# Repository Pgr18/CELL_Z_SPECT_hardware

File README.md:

# CELL_Z_SPECT_hardware
Печатные платы для проекта клеточной импедансной спектроскопии

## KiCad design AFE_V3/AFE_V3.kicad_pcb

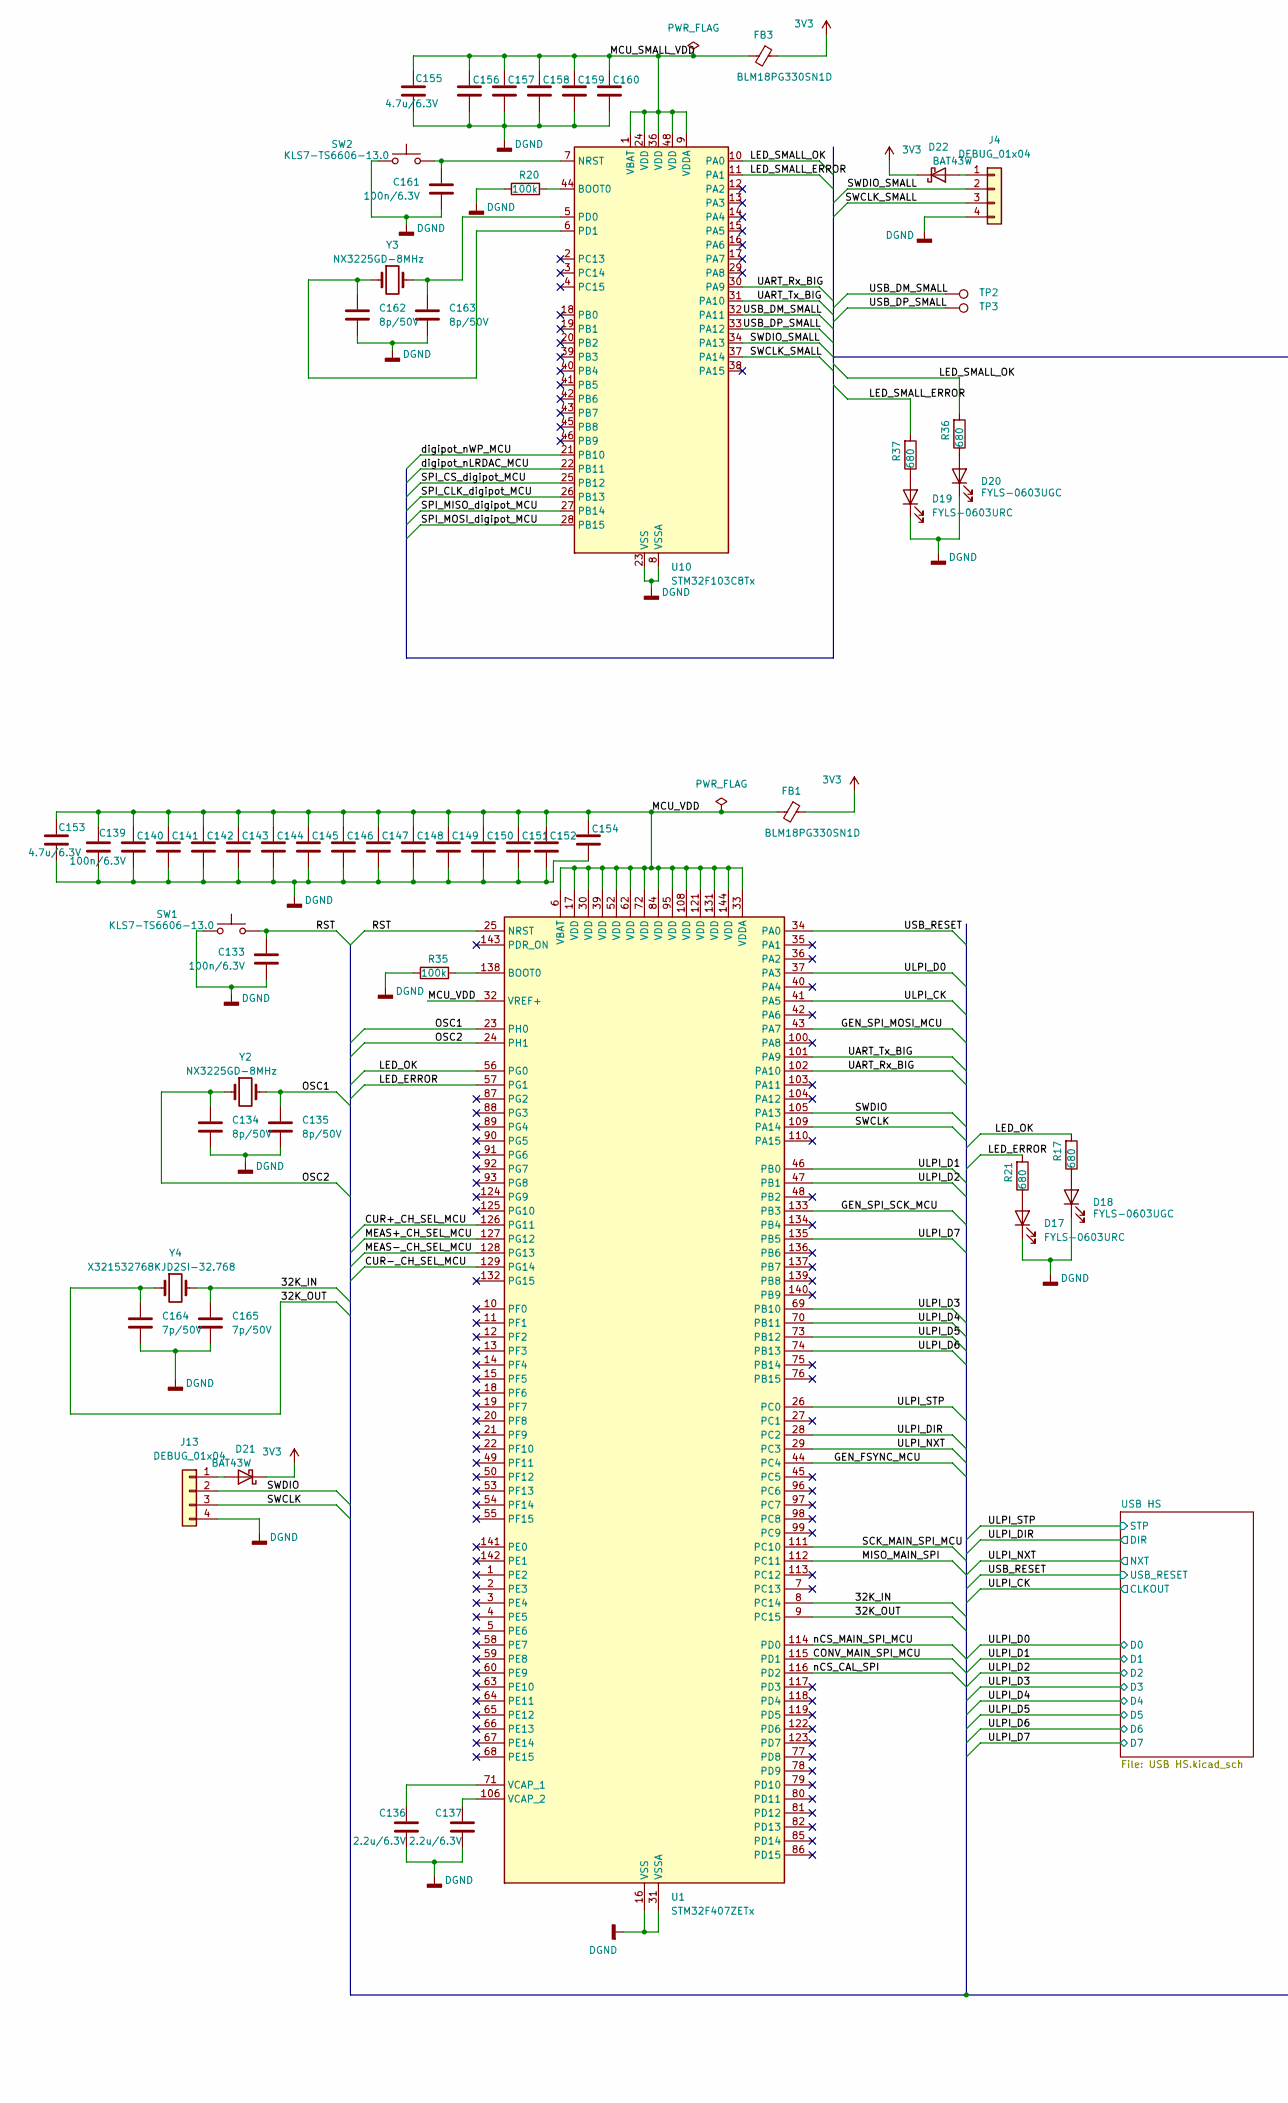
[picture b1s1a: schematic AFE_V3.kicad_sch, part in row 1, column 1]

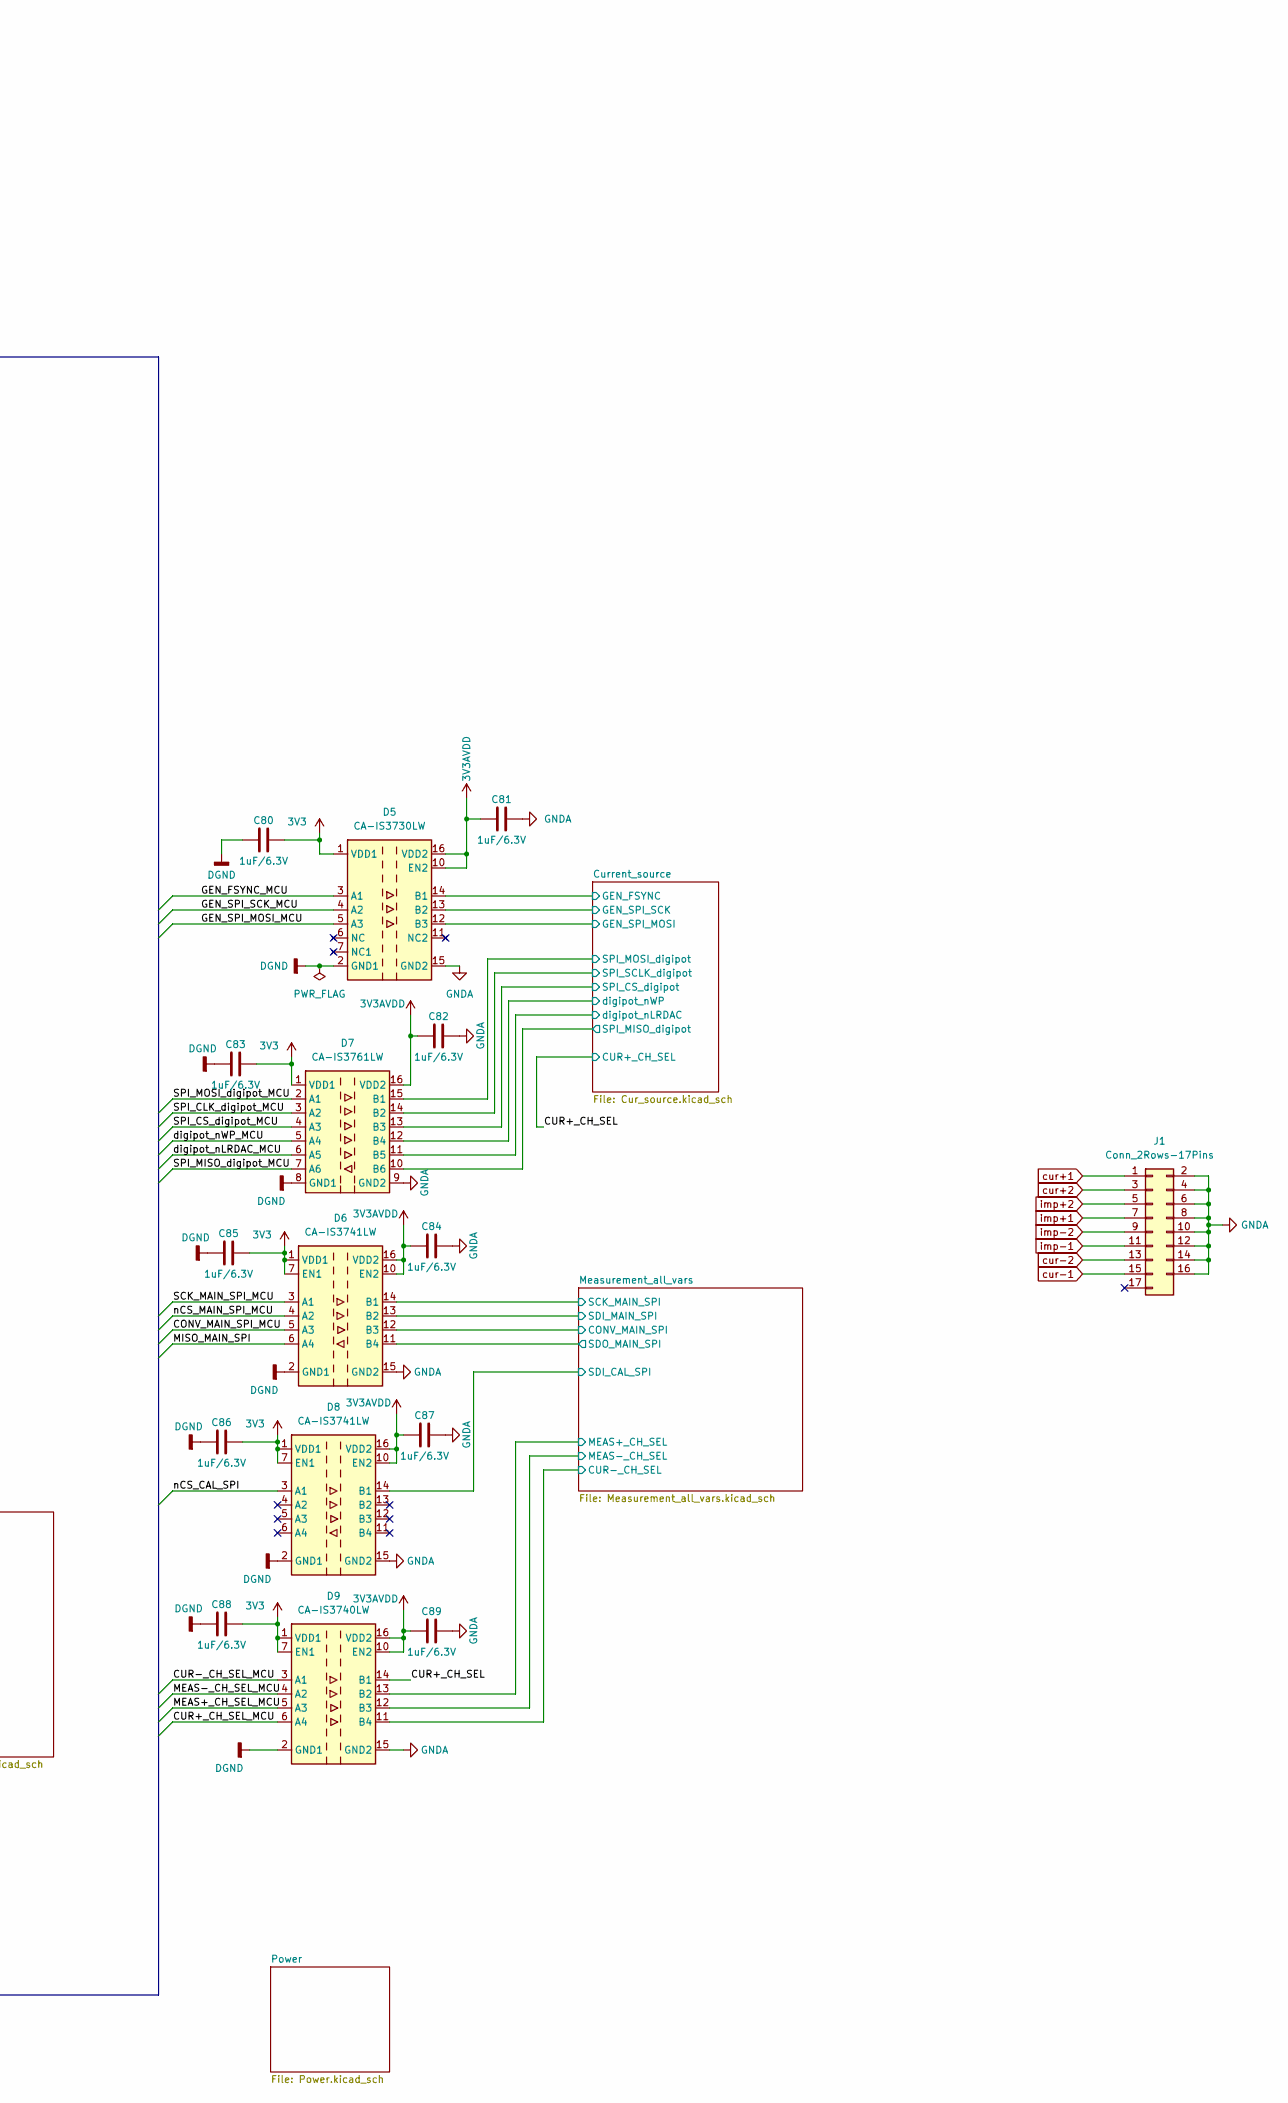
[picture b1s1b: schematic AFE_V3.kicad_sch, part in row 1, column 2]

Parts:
C80, C81, C82, C83, C84, C85, C86, C87, C88, C89: 1uF/6.3V; C_0603_1608Metric_Pad1.08x0.95mm_HandSolder
C133, C139, C140, C141, C142, C143, C144, C145, C146, C147, C148, C149, C150, C151, C152, C154, C156, C157, C158, C159, C160, C161: 100n/6.3V; C_0402_1005Metric
C134, C135, C162, C163: 8p/50V; C_0603_1608Metric_Pad1.08x0.95mm_HandSolder
C136, C137: 2.2u/6.3V; C_0805_2012Metric_Pad1.18x1.45mm_HandSolder
C153, C155: 4.7u/6.3V; C_0805_2012Metric_Pad1.18x1.45mm_HandSolder
C164, C165: 7p/50V; C_0603_1608Metric_Pad1.08x0.95mm_HandSolder
D5: CA-IS3730LW; SOIC-16W_7.5x10.3mm_P1.27mm
D6, D8: CA-IS3741LW; SOIC-16W_7.5x10.3mm_P1.27mm
D7: CA-IS3761LW; SOIC-16W_7.5x10.3mm_P1.27mm
D9: CA-IS3740LW; SOIC-16W_7.5x10.3mm_P1.27mm
D17, D19: FYLS-0603URC; LED_0603_1608Metric_Pad1.05x0.95mm_HandSolder
D18, D20: FYLS-0603UGC; LED_0603_1608Metric_Pad1.05x0.95mm_HandSolder
D21, D22: BAT43W; D_SOD-123
FB1, FB3: BLM18PG330SN1D; L_0603_1608Metric_Pad1.05x0.95mm_HandSolder
J1: Conn_2Rows-17Pins; PinHeader_2x08_P2.54mm_Horizontal
J4, J13: DEBUG_01x04; PinHeader_1x04_P2.54mm_Vertical
R17, R21, R36, R37: 680; R_0603_1608Metric_Pad0.98x0.95mm_HandSolder
R20, R35: 100k; R_0603_1608Metric_Pad0.98x0.95mm_HandSolder
SW1, SW2: KLS7-TS6606-13.0; SW_PUSH_6mm_H4.3mm
TP2, TP3: TestPoint_Pad_D1.0mm
U1: STM32F407ZETx; LQFP-144_20x20mm_P0.5mm
U10: STM32F103C8Tx; LQFP-48_7x7mm_P0.5mm
Y2, Y3: NX3225GD-8MHz; NX3225GD
Y4: X321532768KJD2SI-32.768; Crystal_SMD_3215-2Pin_3.2x1.5mm

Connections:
3V3: C80.2, C83.2, C85.2, C86.2, C88.2, D5.1 (VDD1), D6.1 (VDD1), D6.7 (EN1), D7.1 (VDD1), D8.1 (VDD1), D8.7 (EN1), D9.1 (VDD1), D9.7 (EN1), D21.1 (K), D22.1 (K), FB1.1, FB3.1; also elsewhere on the board
3V3AVDD: C81.1, C82.1, C84.1, C87.1, C89.1, D5.10 (EN2), D5.16 (VDD2), D6.10 (EN2), D6.16 (VDD2), D7.16 (VDD2), D8.10 (EN2), D8.16 (VDD2), D9.10 (EN2), D9.16 (VDD2); also elsewhere on the board
/32K_IN: C165.2, U1.8 (PC14), Y4.2
/32K_OUT: C164.2, U1.9 (PC15), Y4.1
/CONV_MAIN_SPI_MCU: D6.5 (A3), U1.115 (PD1)
/CUR+_CH_SEL: D9.14 (B1); also elsewhere on the board
/CUR+_CH_SEL_MCU: D9.6 (A4), U1.126 (PG11)
/CUR-_CH_SEL_MCU: D9.3 (A1), U1.129 (PG14)
/Current_source/GEN_FSYNC: D5.14 (B1); also elsewhere on the board
/Current_source/GEN_SPI_MOSI: D5.12 (B3); also elsewhere on the board
/Current_source/GEN_SPI_SCK: D5.13 (B2); also elsewhere on the board
/Current_source/SPI_CS_digipot: D7.13 (B3); also elsewhere on the board
/Current_source/SPI_MISO_digipot: D7.10 (B6); also elsewhere on the board
/Current_source/SPI_MOSI_digipot: D7.15 (B1); also elsewhere on the board
/Current_source/SPI_SCLK_digipot: D7.14 (B2); also elsewhere on the board
/Current_source/digipot_nLRDAC: D7.11 (B5); also elsewhere on the board
/Current_source/digipot_nWP: D7.12 (B4); also elsewhere on the board
/GEN_FSYNC_MCU: D5.3 (A1), U1.44 (PC4)
/GEN_SPI_MOSI_MCU: D5.5 (A3), U1.43 (PA7)
/GEN_SPI_SCK_MCU: D5.4 (A2), U1.133 (PB3)
/LED_ERROR: R21.2, U1.57 (PG1)
/LED_OK: R17.2, U1.56 (PG0)
/LED_SMALL_ERROR: R37.2, U10.11 (PA1)
/LED_SMALL_OK: R36.2, U10.10 (PA0)
/MCU_SMALL_VDD: C155.1, C156.2, C157.2, C158.2, C159.2, C160.2, FB3.2, U10.1 (VBAT), U10.9 (VDDA), U10.24 (VDD), U10.36 (VDD), U10.48 (VDD)
/MCU_VDD: C139.2, C140.2, C141.2, C142.2, C143.2, C144.2, C145.2, C146.2, C147.2, C148.2, C149.2, C150.2, C151.2, C152.2, C153.1, C154.2, FB1.2, U1.6 (VBAT), U1.17 (VDD), U1.30 (VDD), U1.32 (VREF+), U1.33 (VDDA), U1.39 (VDD), U1.52 (VDD), U1.62 (VDD), U1.72 (VDD), U1.84 (VDD), U1.95 (VDD), U1.108 (VDD), U1.121 (VDD), U1.131 (VDD), U1.144 (VDD)
/MEAS+_CH_SEL_MCU: D9.5 (A3), U1.127 (PG12)
/MEAS-_CH_SEL_MCU: D9.4 (A2), U1.128 (PG13)
/MISO_MAIN_SPI: D6.6 (A4), U1.112 (PC11)
/Measurement_all_vars/CONV_SPI: D6.12 (B3); also elsewhere on the board
/Measurement_all_vars/CUR-_CH_SEL: D9.11 (B4); also elsewhere on the board
/Measurement_all_vars/MEAS+_CH_SEL: D9.13 (B2); also elsewhere on the board
/Measurement_all_vars/MEAS-_CH_SEL: D9.12 (B3); also elsewhere on the board
/Measurement_all_vars/SDI_CAL_SPI: D8.14 (B1); also elsewhere on the board
/Measurement_all_vars/SDI_MAIN_SPI: D6.13 (B2); also elsewhere on the board
/Measurement_all_vars/SDO_SPI: D6.11 (B4); also elsewhere on the board
/Measurement_all_vars/SPI_CLK: D6.14 (B1); also elsewhere on the board
/OSC1: C135.2, U1.23 (PH0), Y2.2
/OSC2: C134.2, U1.24 (PH1), Y2.1
/RST: C133.2, SW1.2, U1.25 (NRST)
/SCK_MAIN_SPI_MCU: D6.3 (A1), U1.111 (PC10)
/SPI_CLK_digipot_MCU: D7.3 (A2), U10.26 (PB13)
/SPI_CS_digipot_MCU: D7.4 (A3), U10.25 (PB12)
/SPI_MISO_digipot_MCU: D7.7 (A6), U10.27 (PB14)
/SPI_MOSI_digipot_MCU: D7.2 (A1), U10.28 (PB15)
/SWCLK: J13.3, U1.109 (PA14)
/SWCLK_SMALL: J4.3, U10.37 (PA14)
/SWDIO: J13.2, U1.105 (PA13)
/SWDIO_SMALL: J4.2, U10.34 (PA13)
/UART_Rx_BIG: U1.102 (PA10), U10.30 (PA9)
/UART_Tx_BIG: U1.101 (PA9), U10.31 (PA10)
/ULPI_CK: U1.41 (PA5); also elsewhere on the board
/ULPI_D0: U1.37 (PA3); also elsewhere on the board
/ULPI_D1: U1.46 (PB0); also elsewhere on the board
/ULPI_D2: U1.47 (PB1); also elsewhere on the board
/ULPI_D3: U1.69 (PB10); also elsewhere on the board
/ULPI_D4: U1.70 (PB11); also elsewhere on the board
/ULPI_D5: U1.73 (PB12); also elsewhere on the board
/ULPI_D6: U1.74 (PB13); also elsewhere on the board
/ULPI_D7: U1.135 (PB5); also elsewhere on the board
/ULPI_DIR: U1.28 (PC2); also elsewhere on the board
/ULPI_NXT: U1.29 (PC3); also elsewhere on the board
/ULPI_STP: U1.26 (PC0); also elsewhere on the board
/USB_DM_SMALL: TP2.1, U10.32 (PA11)
/USB_DP_SMALL: TP3.1, U10.33 (PA12)
/USB_RESET: U1.34 (PA0); also elsewhere on the board
/digipot_nLRDAC_MCU: D7.6 (A5), U10.22 (PB11)
/digipot_nWP_MCU: D7.5 (A4), U10.21 (PB10)
/nCS_CAL_SPI: D8.3 (A1), U1.116 (PD2)
/nCS_MAIN_SPI_MCU: D6.4 (A2), U1.114 (PD0)
DGND: C80.1, C83.1, C85.1, C86.1, C88.1, C133.1, C134.1, C135.1, C136.2, C137.2, C139.1, C140.1, C141.1, C142.1, C143.1, C144.1, C145.1, C146.1, C147.1, C148.1, C149.1, C150.1, C151.1, C152.1, C153.2, C154.1, C155.2, C156.1, C157.1, C158.1, C159.1, C160.1, C161.1, C162.1, C163.1, C164.1, C165.1, D5.2 (GND1), D5.8 (GND1), D6.2 (GND1), D6.8 (GND1), D7.8 (GND1), D8.2 (GND1), D8.8 (GND1), D9.2 (GND1), D9.8 (GND1), D17.1 (K), D18.1 (K), D19.1 (K), D20.1 (K), J4.4, J13.4, R20.1, R35.1, SW1.1, SW2.1, U1.16 (VSS), U1.31 (VSSA), U1.38 (VSS), U1.51 (VSS), U1.61 (VSS), U1.83 (VSS), U1.94 (VSS), U1.107 (VSS), U1.120 (VSS), U1.130 (VSS), U10.8 (VSSA), U10.23 (VSS), U10.35 (VSS), U10.47 (VSS); also elsewhere on the board
GNDA: C81.2, C82.2, C84.2, C87.2, C89.2, D5.9 (GND2), D5.15 (GND2), D6.9 (GND2), D6.15 (GND2), D7.9 (GND2), D8.9 (GND2), D8.15 (GND2), D9.9 (GND2), D9.15 (GND2), J1.2, J1.4, J1.6, J1.8, J1.10, J1.12, J1.14, J1.16; also elsewhere on the board
unnamed: D17.2 (A), R21.1
unnamed: D18.2 (A), R17.1
unnamed: D19.2 (A), R37.1
unnamed: D20.2 (A), R36.1
unnamed: D21.2 (A), J13.1
unnamed: D22.2 (A), J4.1
unnamed: R35.2, U1.138 (BOOT0)
unnamed: C136.1, U1.71 (VCAP_1)
unnamed: C137.1, U1.106 (VCAP_2)
unnamed: R20.2, U10.44 (BOOT0)
unnamed: C161.2, SW2.2, U10.7 (NRST)
unnamed: C163.2, U10.5 (PD0), Y3.2
unnamed: C162.2, U10.6 (PD1), Y3.1
cur+1: J1.1; also elsewhere on the board
cur+2: J1.3; also elsewhere on the board
cur-1: J1.15; also elsewhere on the board
cur-2: J1.13; also elsewhere on the board
imp+1: J1.7; also elsewhere on the board
imp+2: J1.5; also elsewhere on the board
imp-1: J1.11; also elsewhere on the board
imp-2: J1.9; also elsewhere on the board

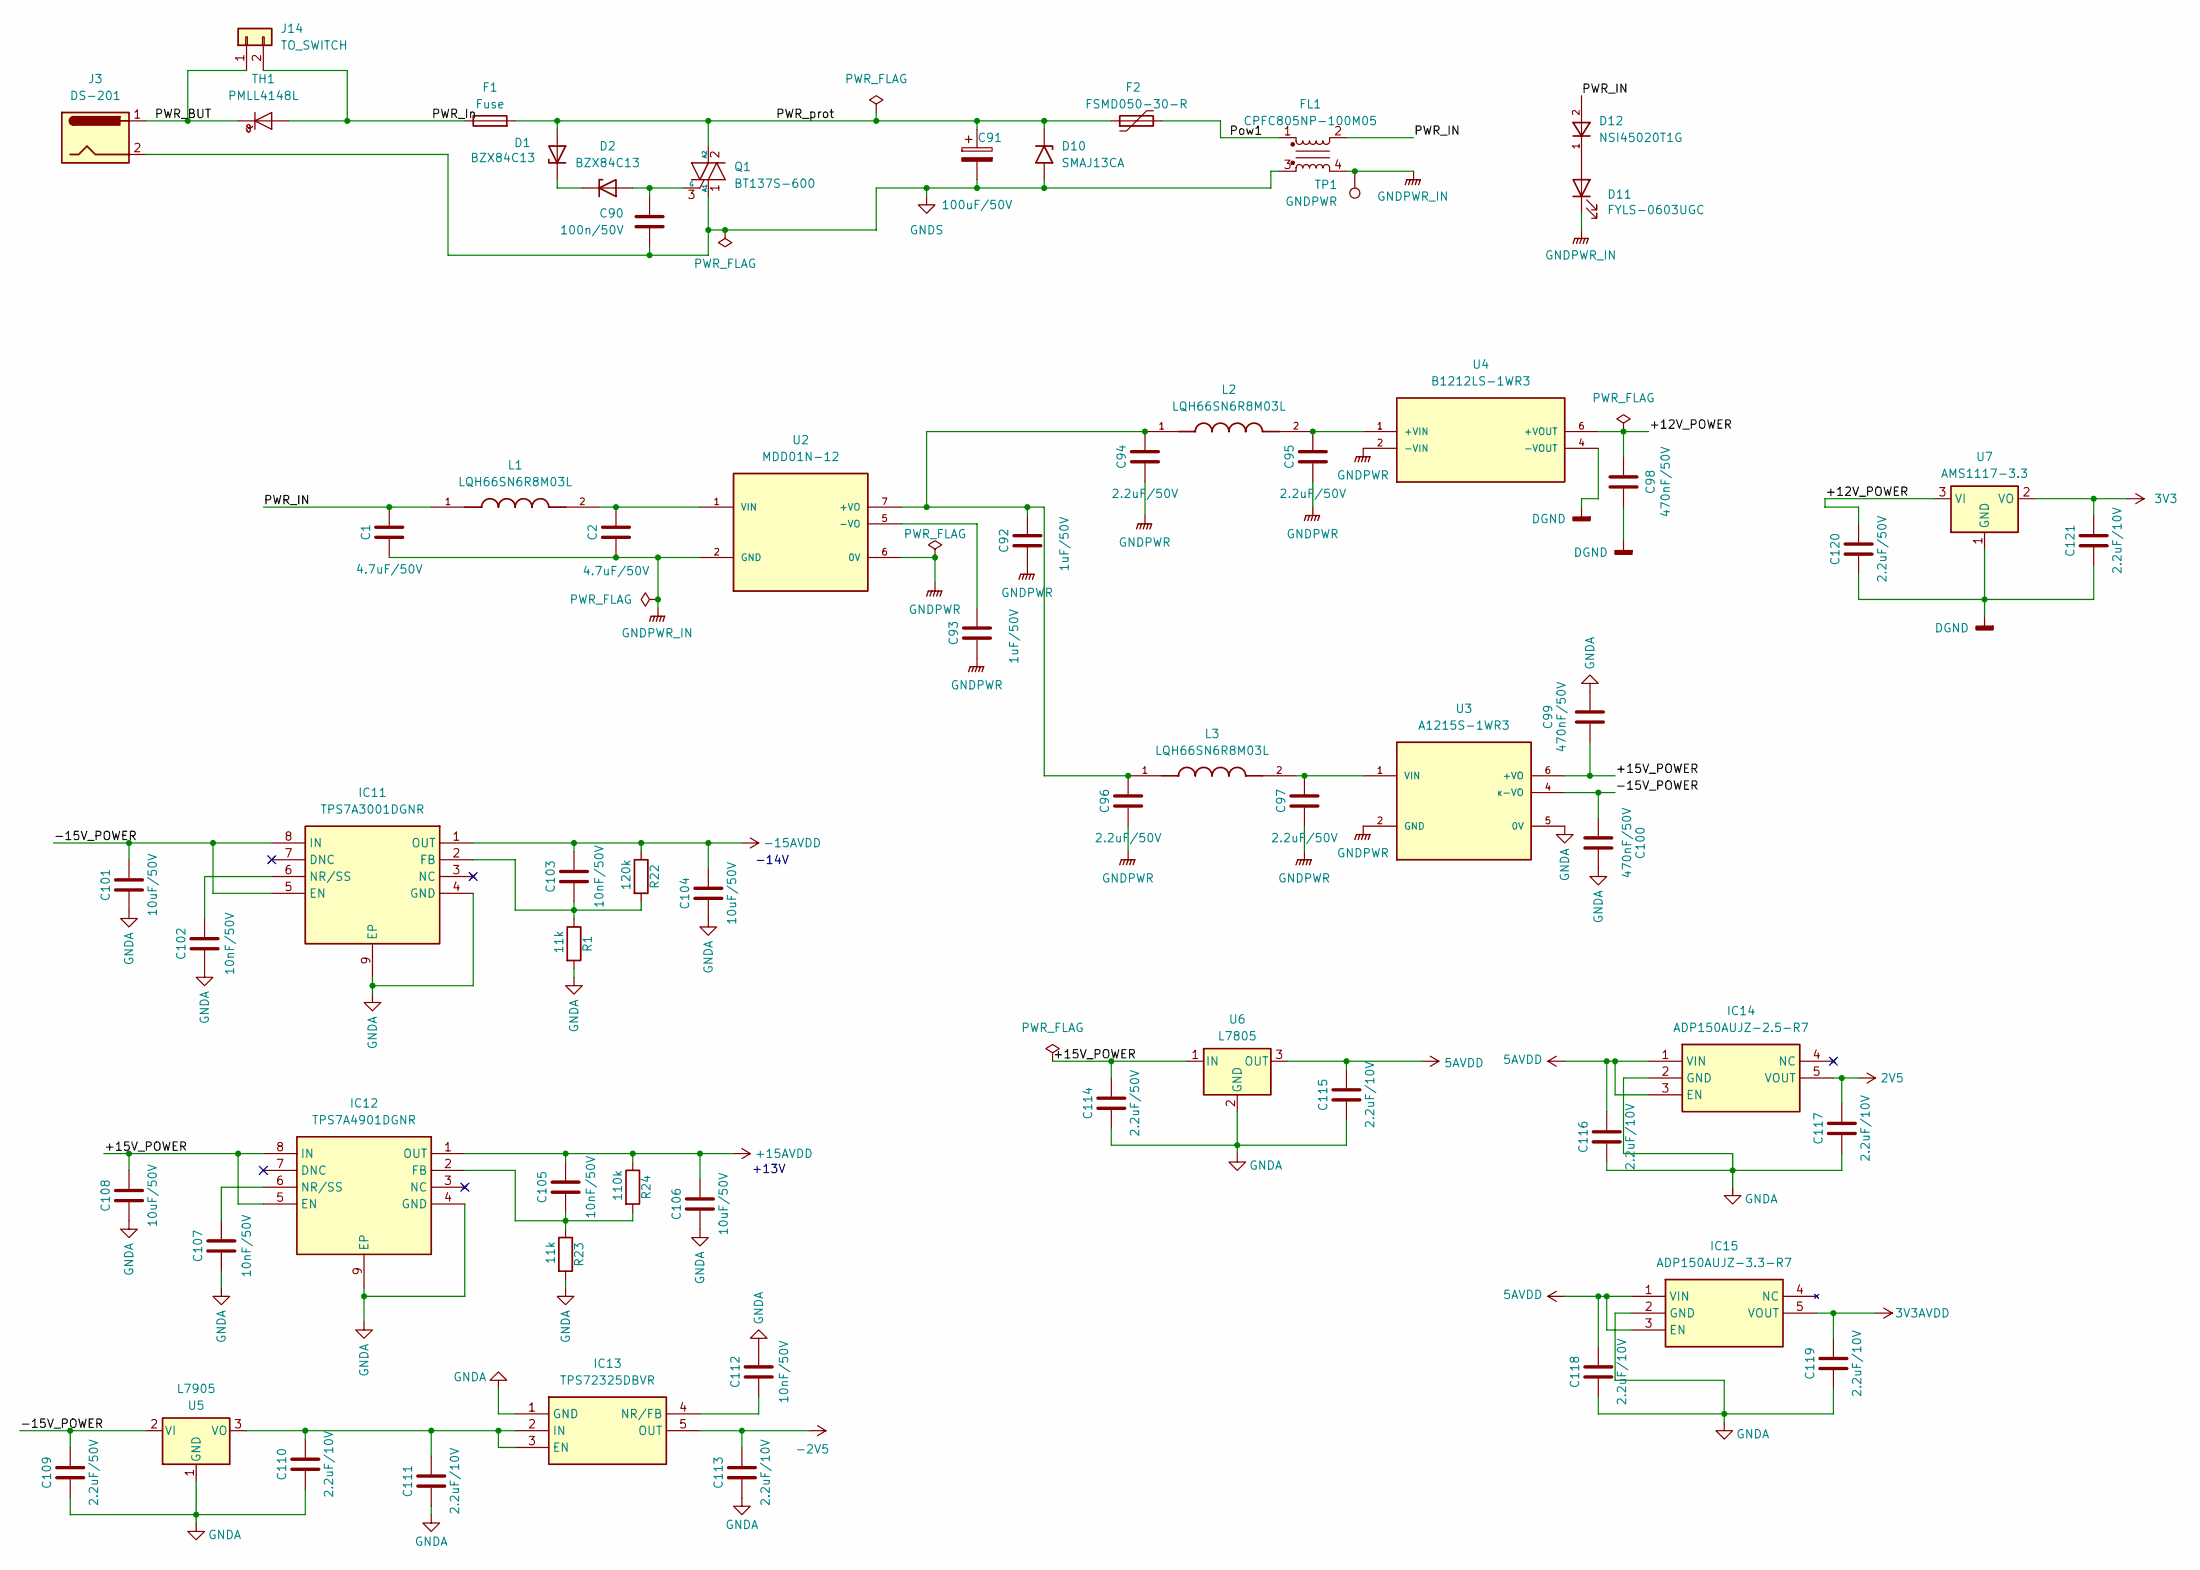
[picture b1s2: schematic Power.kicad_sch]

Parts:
C1, C2: 4.7uF/50V; C_0805_2012Metric_Pad1.18x1.45mm_HandSolder
C90: 100n/50V; C_0603_1608Metric_Pad1.08x0.95mm_HandSolder
C91: 100uF/50V; CP_Radial_D8.0mm_P3.50mm
C92, C93: 1uF/50V; C_0805_2012Metric_Pad1.18x1.45mm_HandSolder
C94, C95, C96, C97, C109, C114, C120: 2.2uF/50V; C_0805_2012Metric_Pad1.18x1.45mm_HandSolder
C98, C99, C100: 470nF/50V; C_0805_2012Metric_Pad1.18x1.45mm_HandSolder
C101, C104, C106, C108: 10uF/50V; C_0805_2012Metric_Pad1.18x1.45mm_HandSolder
C102, C103, C105, C107, C112: 10nF/50V; C_0603_1608Metric_Pad1.08x0.95mm_HandSolder
C110, C111, C113, C115, C116, C117, C118, C119, C121: 2.2uF/10V; C_0805_2012Metric_Pad1.18x1.45mm_HandSolder
D1, D2: BZX84C13; SOT-23
D10: SMAJ13CA; D_SMA
D11: FYLS-0603UGC; LED_0603_1608Metric_Pad1.05x0.95mm_HandSolder
D12: NSI45020T1G; SOD3716X135N; PARTREV 6
F1: Fuse; Fuseholder_Cylinder-5x20mm_Stelvio-Kontek_PTF78_Horizontal_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
F2: FSMD050-30-R; Fuse_1812_4532Metric_Pad1.30x3.40mm_HandSolder
FL1: CPFC805NP-100M05; CPFC805
IC11: TPS7A3001DGNR; SOP65P490X110-9N; Manufacturer_Part_Number TPS7A3001DGNR; Mouser Part Number 595-TPS7A3001DGNR
IC12: TPS7A4901DGNR; SOP65P490X110-9N; Manufacturer_Part_Number TPS7A4901DGNR; Mouser Part Number 595-TPS7A4901DGNR
IC13: TPS72325DBVR; SOT95P280X145-5N; Manufacturer_Part_Number TPS72325DBVR; Mouser Part Number 595-TPS72325DBVR
IC14: ADP150AUJZ-2.5-R7; SOT95P280X100-5N; Manufacturer_Part_Number ADP150AUJZ-2.5-R7; Mouser Part Number 584-ADP150AUJZ-2.5R7
IC15: ADP150AUJZ-3.3-R7; SOT95P280X100-5N; Manufacturer_Part_Number ADP150AUJZ-2.5-R7; Mouser Part Number 584-ADP150AUJZ-2.5R7
J3: DS-201; DS201b
J14: TO_SWITCH; Samtec_HPM-02-01-x-S_Straight_1x02_Pitch5.08mm
L1, L2, L3: LQH66SN6R8M03L; IND_LQH66SN6R8M03L; PARTREV N/A
Q1: BT137S-600; TO-252-2
R1, R23: 11k; R_0603_1608Metric_Pad0.98x0.95mm_HandSolder
R22: 120k; R_0603_1608Metric_Pad0.98x0.95mm_HandSolder
R24: 110k; R_0603_1608Metric_Pad0.98x0.95mm_HandSolder
TH1: PMLL4148L; D_MiniMELF
TP1: GNDPWR; TestPoint_Loop_D2.60mm_Drill1.6mm_Beaded
U2: MDD01N-12; CONV_PEM2-S12-D12-S
U3: A1215S-1WR3; CONV_PDM2-S24-D3-S; PARTREV 1.03
U4: B1212LS-1WR3; CONV_PCN1-S5-S15-S; PARTREV 1.0
U5: L7905; TO-263-2
U6: L7805; TO-263-2
U7: AMS1117-3.3; SOT-223-3_TabPin2

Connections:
2V5: C117.1, IC14.5 (VOUT); also elsewhere on the board
3V3: C121.1, U7.2 (VO); also elsewhere on the board
3V3AVDD: C119.1, IC15.5 (VOUT); also elsewhere on the board
5AVDD: C115.1, C116.1, C118.1, IC14.1 (VIN), IC14.3 (EN), IC15.1 (VIN), IC15.3 (EN), U6.3 (OUT); also elsewhere on the board
+15AVDD: C105.1, C106.1, IC12.1 (OUT), R24.1; also elsewhere on the board
-2V5: C113.1, IC13.5 (OUT); also elsewhere on the board
-15AVDD: C103.1, C104.1, IC11.1 (OUT), R22.1; also elsewhere on the board
/Power/+12V_POWER: C98.1, C120.1, U4.6 (+VOUT), U7.3 (VI)
/Power/+15V_POWER: C99.2, C108.1, C114.1, IC12.5 (EN), IC12.8 (IN), U3.6 (+VO), U6.1 (IN)
/Power/-15V_POWER: C100.2, C101.1, C109.1, IC11.5 (EN), IC11.8 (IN), U3.4 (к-VO), U5.2 (VI)
/Power/PWR_BUT: J3.1, J14.1, TH1.1 (K)
/Power/PWR_IN: C1.1, D12.2, FL1.2, L1.1
/Power/PWR_In: F1.1, J14.2, TH1.2 (A)
/Power/PWR_prot: C91.1, D1.1 (A), D10.1 (A1), F1.2, F2.1, Q1.2 (A2)
/Power/Pow1: F2.2, FL1.1
DGND: C98.2, C120.2, C121.2, U4.4 (-VOUT), U7.1 (GND); also elsewhere on the board
GNDA: C99.1, C100.1, C101.2, C102.2, C104.2, C106.2, C107.2, C108.2, C109.2, C110.2, C111.2, C112.1, C113.2, C114.2, C115.2, C116.2, C117.2, C118.2, C119.2, IC11.4 (GND), IC11.9 (EP), IC12.4 (GND), IC12.9 (EP), IC13.1 (GND), IC14.2 (GND), IC15.2 (GND), R1.2, R23.2, U3.5 (0V), U5.1 (GND), U6.2 (GND); also elsewhere on the board
GNDPWR: C92.2, C93.2, C94.2, C95.2, C96.2, C97.2, U2.6 (0V), U3.2 (GND), U4.2 (-VIN)
GNDPWR_IN: C1.2, C2.2, D11.1 (K), FL1.4, TP1.1, U2.2 (GND)
GNDS: C90.2, C91.2, D10.2 (A2), FL1.3, J3.2, Q1.1 (A1)
unnamed: D1.3 (K), D2.3 (K)
unnamed: C90.1, D2.1 (A), Q1.3 (G)
unnamed: D11.2 (A), D12.1
unnamed: C103.2, IC11.2 (FB), R1.1, R22.2
unnamed: C102.1, IC11.6 (NR/SS)
unnamed: C105.2, IC12.2 (FB), R23.1, R24.2
unnamed: C107.1, IC12.6 (NR/SS)
unnamed: C110.1, C111.1, IC13.2 (IN), IC13.3 (EN), U5.3 (VO)
unnamed: C112.2, IC13.4 (NR/FB)
unnamed: C92.1, C94.1, C96.1, L2.1, L3.1, U2.7 (+VO)
unnamed: C93.1, U2.5 (-VO)
unnamed: C2.1, L1.2, U2.1 (VIN)
unnamed: C97.1, L3.2, U3.1 (VIN)
unnamed: C95.1, L2.2, U4.1 (+VIN)

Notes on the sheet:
+13V
-14V

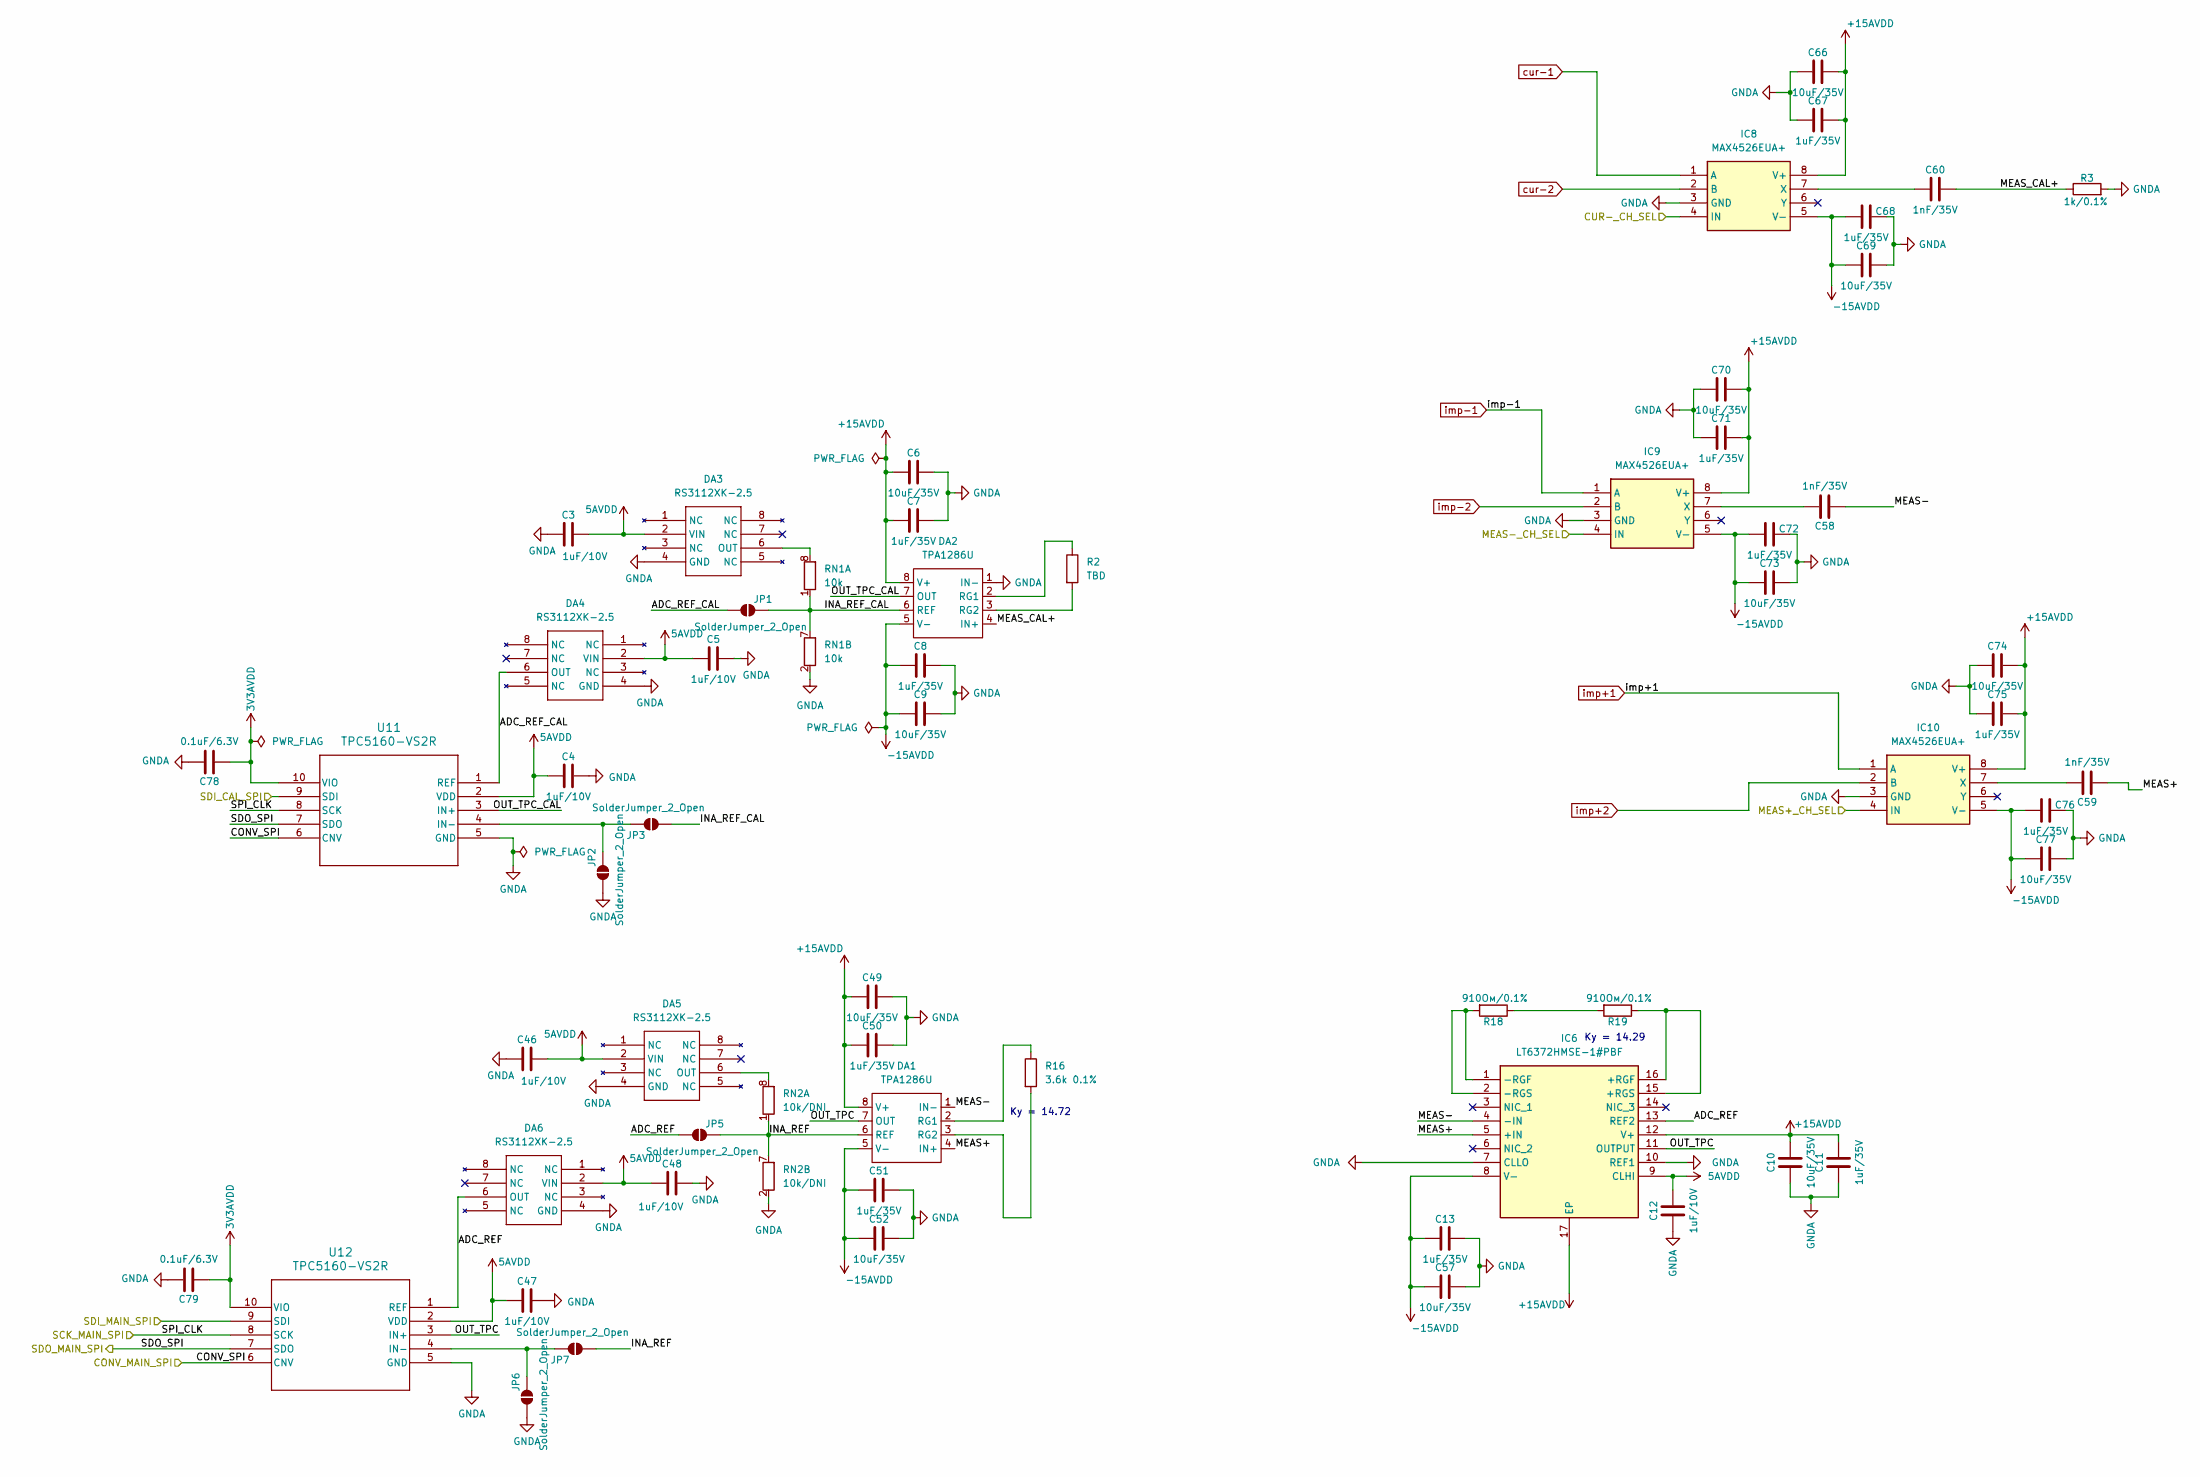
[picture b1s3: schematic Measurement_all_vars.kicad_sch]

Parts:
C3, C4, C5, C12, C46, C47, C48: 1uF/10V; C_0603_1608Metric_Pad1.08x0.95mm_HandSolder
C6, C9, C10, C49, C52, C57, C66, C69, C70, C73, C74, C77: 10uF/35V; C_0805_2012Metric_Pad1.18x1.45mm_HandSolder
C7, C8, C11, C13, C50, C51, C67, C68, C71, C72, C75, C76: 1uF/35V; C_0603_1608Metric_Pad1.08x0.95mm_HandSolder
C58, C59, C60: 1nF/35V; C_0603_1608Metric_Pad1.08x0.95mm_HandSolder
C78, C79: 0.1uF/6.3V; C_0603_1608Metric_Pad1.08x0.95mm_HandSolder
DA1, DA2: TPA1286U; MSOP-8_3x3mm_P0.65mm
DA3, DA4, DA5, DA6: RS3112XK-2.5; SOIC-8_3.9x4.9mm_P1.27mm
IC6: LT6372HMSE-1#PBF; SOP50P490X110-17N; Manufacturer_Part_Number LT6372HMSE-1#PBF; Mouser Part Number 584-LT6372HMSE-1#PBF
IC8, IC9, IC10: MAX4526EUA+; SOIC127P600X175-8N; Manufacturer_Part_Number MAX4526CSA+; Mouser Part Number 700-MAX4526CSA
JP1, JP2, JP3, JP5, JP6, JP7: SolderJumper_2_Open; SolderJumper-2_P1.3mm_Open_TrianglePad1.0x1.5mm
R2: TBD; R_0805_2012Metric_Pad1.20x1.40mm_HandSolder
R3: 1k/0.1%; R_0603_1608Metric_Pad0.98x0.95mm_HandSolder
R16: 3.6k 0.1%; R_0805_2012Metric_Pad1.20x1.40mm_HandSolder
R18, R19: 910Ом/0.1%; R_0603_1608Metric_Pad0.98x0.95mm_HandSolder
RN1: 10k; R_Array_Convex_4x0603
RN2: 10k/DNI; R_Array_Convex_4x0603
U11, U12: TPC5160-VS2R; VS2MSOP-10-A_TPK

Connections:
3V3AVDD: C78.1, C79.1, U11.10 (VIO), U12.10 (VIO); also elsewhere on the board
5AVDD: C3.1, C4.1, C5.1, C12.2, C46.1, C47.1, C48.1, DA3.2 (VIN), DA4.2 (VIN), DA5.2 (VIN), DA6.2 (VIN), IC6.9 (CLHI), U11.2 (VDD), U12.2 (VDD); also elsewhere on the board
+15AVDD: C6.2, C7.2, C10.2, C11.2, C49.2, C50.2, C66.2, C67.2, C70.2, C71.2, C74.2, C75.2, DA1.8 (V+), DA2.8 (V+), IC6.12 (V+), IC6.17 (EP), IC8.8 (V+), IC9.8 (V+), IC10.8 (V+); also elsewhere on the board
-15AVDD: C8.2, C9.2, C13.2, C51.2, C52.2, C57.2, C68.2, C69.2, C72.2, C73.2, C76.2, C77.2, DA1.5 (V-), DA2.5 (V-), IC6.8 (V-), IC8.5 (V-), IC9.5 (V-), IC10.5 (V-); also elsewhere on the board
/Measurement_all_vars/ADC_REF: DA6.6 (OUT), IC6.13 (REF2), JP5.1 (A), U12.1 (REF)
/Measurement_all_vars/ADC_REF_CAL: DA4.6 (OUT), JP1.1 (A), U11.1 (REF)
/Measurement_all_vars/CONV_SPI: U11.6 (CNV), U12.6 (CNV); also elsewhere on the board
/Measurement_all_vars/CUR-_CH_SEL: IC8.4 (IN); also elsewhere on the board
/Measurement_all_vars/INA_REF: DA1.6 (REF), JP5.2 (B), JP7.1 (A), RN2.1 (R1.1), RN2.7 (R2.2)
/Measurement_all_vars/INA_REF_CAL: DA2.6 (REF), JP1.2 (B), JP3.1 (A), RN1.1 (R1.1), RN1.7 (R2.2)
/Measurement_all_vars/MEAS+: C59.1, DA1.4 (IN+), IC6.5 (+IN)
/Measurement_all_vars/MEAS+_CH_SEL: IC10.4 (IN); also elsewhere on the board
/Measurement_all_vars/MEAS-: C58.1, DA1.1 (IN-), IC6.4 (-IN)
/Measurement_all_vars/MEAS-_CH_SEL: IC9.4 (IN); also elsewhere on the board
/Measurement_all_vars/MEAS_CAL+: C60.2, DA2.4 (IN+), R3.1
/Measurement_all_vars/OUT_TPC: DA1.7 (OUT), IC6.11 (OUTPUT), U12.3 (IN+)
/Measurement_all_vars/OUT_TPC_CAL: DA2.7 (OUT), U11.3 (IN+)
/Measurement_all_vars/SDI_CAL_SPI: U11.9 (SDI); also elsewhere on the board
/Measurement_all_vars/SDI_MAIN_SPI: U12.9 (SDI); also elsewhere on the board
/Measurement_all_vars/SDO_SPI: U11.7 (SDO), U12.7 (SDO); also elsewhere on the board
/Measurement_all_vars/SPI_CLK: U11.8 (SCK), U12.8 (SCK); also elsewhere on the board
GNDA: C3.2, C4.2, C5.2, C6.1, C7.1, C8.1, C9.1, C10.1, C11.1, C12.1, C13.1, C46.2, C47.2, C48.2, C49.1, C50.1, C51.1, C52.1, C57.1, C66.1, C67.1, C68.1, C69.1, C70.1, C71.1, C72.1, C73.1, C74.1, C75.1, C76.1, C77.1, C78.2, C79.2, DA2.1 (IN-), DA3.4 (GND), DA4.4 (GND), DA5.4 (GND), DA6.4 (GND), IC6.7 (CLLO), IC6.10 (REF1), IC8.3 (GND), IC9.3 (GND), IC10.3 (GND), JP2.1 (A), JP6.1 (A), R3.2, RN1.2 (R2.1), RN2.2 (R2.1), U11.5 (GND), U12.5 (GND); also elsewhere on the board
unnamed: DA1.2 (RG1), R16.1
unnamed: DA1.3 (RG2), R16.2
unnamed: DA2.2 (RG1), R2.1
unnamed: DA2.3 (RG2), R2.2
unnamed: DA3.6 (OUT), RN1.8 (R1.2)
unnamed: DA5.6 (OUT), RN2.8 (R1.2)
unnamed: IC6.15 (+RGS), IC6.16 (+RGF), R19.1
unnamed: IC6.1 (-RGF), IC6.2 (-RGS), R18.2
unnamed: C60.1, IC8.7 (X)
unnamed: C58.2, IC9.7 (X)
unnamed: C59.2, IC10.7 (X)
unnamed: JP2.2 (B), JP3.2 (B), U11.4 (IN-)
unnamed: JP6.2 (B), JP7.2 (B), U12.4 (IN-)
unnamed: R18.1, R19.2
cur-1: IC8.1 (A); also elsewhere on the board
cur-2: IC8.2 (B); also elsewhere on the board
imp+1: IC10.1 (A); also elsewhere on the board
imp+2: IC10.2 (B); also elsewhere on the board
imp-1: IC9.1 (A); also elsewhere on the board
imp-2: IC9.2 (B); also elsewhere on the board

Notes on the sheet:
Ку = 14.72
Ку = 14.29
